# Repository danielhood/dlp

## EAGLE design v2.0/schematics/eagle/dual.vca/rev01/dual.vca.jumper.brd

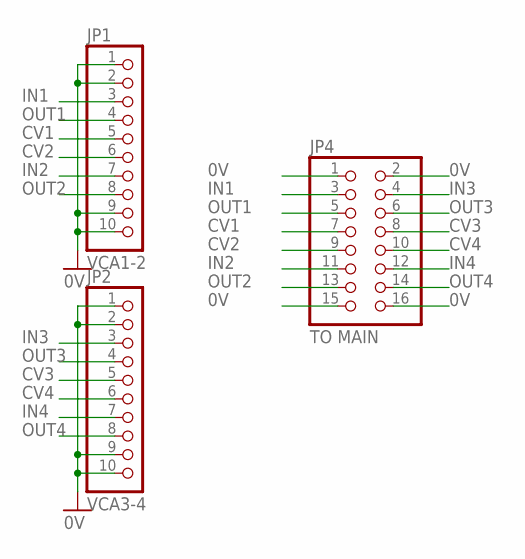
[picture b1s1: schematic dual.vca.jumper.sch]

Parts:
JP1: VCA1-2; 1X10
JP2: VCA3-4; 1X10
JP4: TO MAIN; 2X08

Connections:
0V: JP1.1, JP1.2, JP1.9, JP1.10, JP2.1, JP2.2, JP2.9, JP2.10, JP4.1, JP4.2, JP4.15, JP4.16
CV1: JP1.5, JP4.7
CV2: JP1.6, JP4.9
CV3: JP2.5, JP4.8
CV4: JP2.6, JP4.10
IN1: JP1.3, JP4.3
IN2: JP1.7, JP4.11
IN3: JP2.3, JP4.4
IN4: JP2.7, JP4.12
OUT1: JP1.4, JP4.5
OUT2: JP1.8, JP4.13
OUT3: JP2.4, JP4.6
OUT4: JP2.8, JP4.14

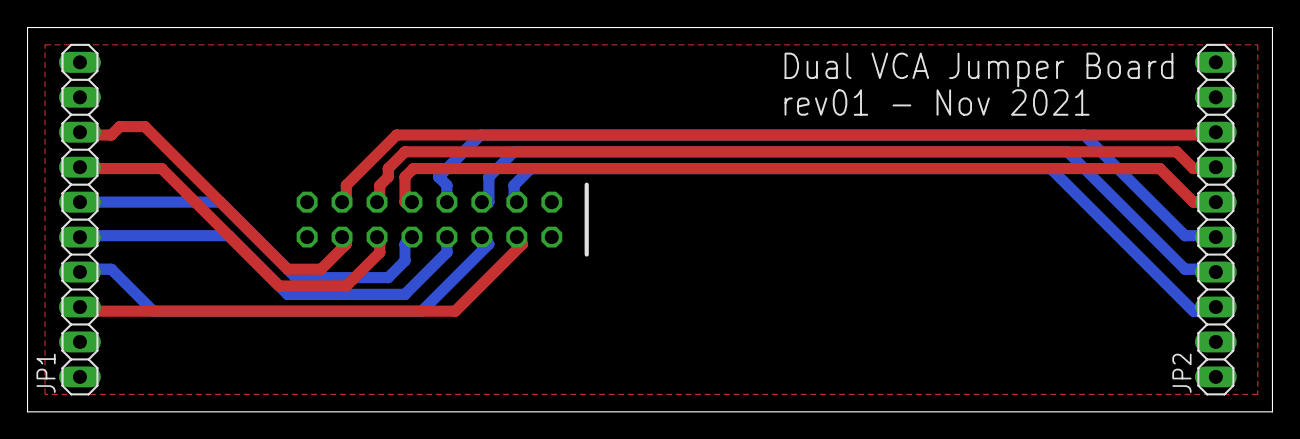
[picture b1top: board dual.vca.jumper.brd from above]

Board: 2 copper layers, 90.5 x 27.9 mm, 3 parts (1 on the bottom side), 13 nets.

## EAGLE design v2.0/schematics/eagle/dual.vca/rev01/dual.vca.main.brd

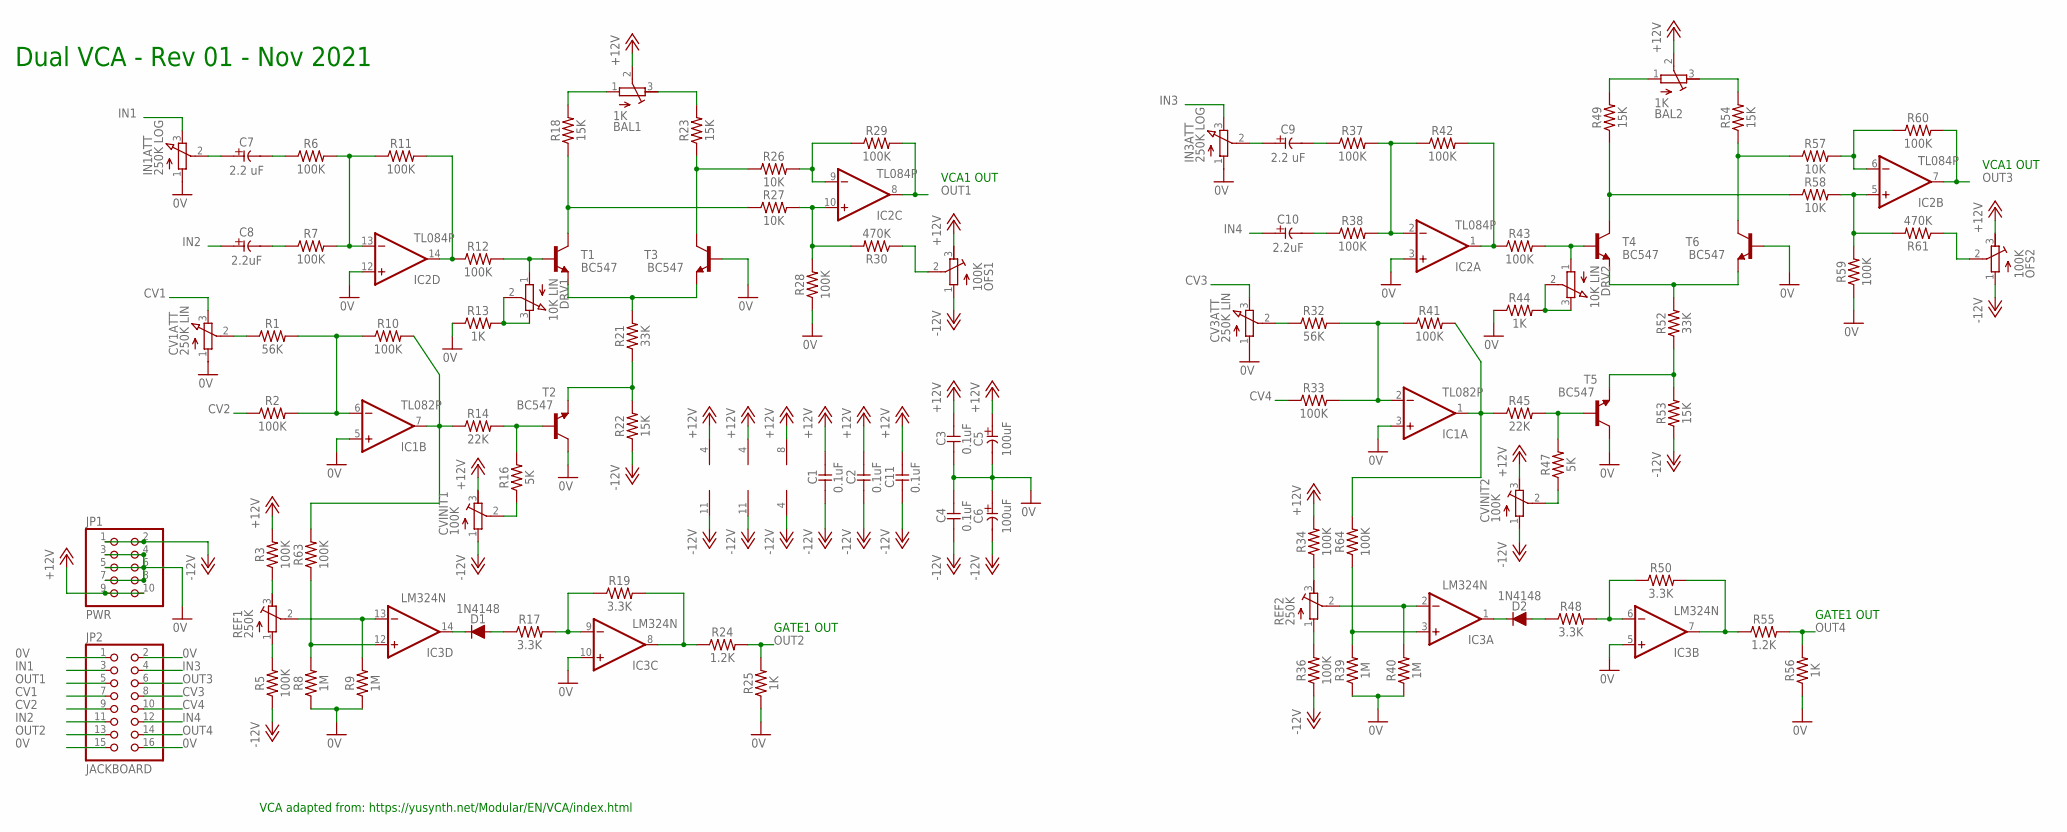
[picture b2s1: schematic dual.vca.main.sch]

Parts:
BAL1, BAL2: 1K; RTRIM3339P
C1, C2, C3, C4, C11: 0.1uF; C025-024X044
C5, C6: 100uF; E5-8,5
C7, C9: 2.2 uF; E2-5
C8, C10: 2.2uF; E2-5
CV1ATT, CV3ATT: 250K LIN; 3RP/1610N
CVINIT1, CVINIT2: 100K; RTRIM3339P
D1, D2: 1N4148; DO34-5
DRV1, DRV2: 10K LIN; 3RP/1610N
IC1: TL082P; DIL08
IC2: TL084P; DIL14
IC3: LM324N; DIL14
IN1ATT, IN3ATT: 250K LOG; 3RP/1610N
JP1: PWR; 2X05
JP2: JACKBOARD; 2X08
OFS1, OFS2: 100K; RTRIM3339P
R1, R32: 56K; 0207/7
R2, R3, R5, R6, R7, R10, R11, R12, R28, R29, R33, R34, R36, R37, R38, R41, R42, R43, R59, R60, R63, R64: 100K; 0207/7
R8, R9, R39, R40: 1M; 0207/7
R13, R25, R44, R56: 1K; 0207/7
R14, R45: 22K; 0207/7
R16, R47: 5K; 0207/7
R17, R19, R48, R50: 3.3K; 0207/7
R18, R22, R23, R49, R53, R54: 15K; 0207/7
R21, R52: 33K; 0207/7
R24, R55: 1.2K; 0207/7
R26, R27, R57, R58: 10K; 0207/7
R30, R61: 470K; 0207/7
REF1, REF2: 250K; RTRIM3339P
T1, T2, T3, T4, T5, T6: BC547; TO92

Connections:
0V: C3.2, C4.1, C5.-, C6.+, CV1ATT.1 (A), CV3ATT.1 (A), IC1.3 (+IN), IC1.5 (+IN), IC2.3 (+IN), IC2.12 (+IN), IC3.5 (+IN), IC3.10 (+IN), IN1ATT.1 (A), IN3ATT.1 (A), JP1.3, JP1.4, JP1.5, JP1.6, JP1.7, JP1.8, JP2.1, JP2.2, JP2.15, JP2.16, R8.1, R9.1, R13.1, R25.1, R28.1, R39.1, R40.1, R44.1, R56.1, R59.1, T2.3 (C), T3.2 (B), T5.3 (C), T6.2 (B)
+12V: BAL1.2 (S), BAL2.2 (S), C1.1, C2.1, C3.1, C5.+, C11.1, CVINIT1.3 (E), CVINIT2.3 (E), IC1.8 (V+), IC2.4 (V+), IC3.4 (V+), JP1.9, JP1.10, OFS1.3 (E), OFS2.3 (E), R3.2, R34.2
-12V: C1.2, C2.2, C4.2, C6.-, C11.2, CVINIT1.1 (A), CVINIT2.1 (A), IC1.4 (V-), IC2.11 (V-), IC3.11 (V-), JP1.1, JP1.2, OFS1.1 (A), OFS2.1 (A), R5.1, R22.1, R36.1, R53.1
CV1: CV1ATT.3 (E), JP2.7
CV2: JP2.9, R2.1
CV3: CV3ATT.3 (E), JP2.8
CV4: JP2.10, R33.1
IN1: IN1ATT.3 (E), JP2.3
IN2: C8.+, JP2.11
IN3: IN3ATT.3 (E), JP2.4
IN4: C10.+, JP2.12
unnamed: IC2.13 (-IN), R6.2, R7.2, R11.1
unnamed: IC2.9 (-IN), R26.2, R29.1
unnamed: IC2.14 (OUT), R11.2, R12.1
unnamed: DRV1.1 (A), R12.2, T1.2 (B)
unnamed: R18.1, R27.1, T1.3 (C)
unnamed: BAL1.1 (A), R18.2
unnamed: BAL1.3 (E), R23.2
unnamed: R23.1, R26.1, T3.3 (C)
unnamed: R21.2, T1.1 (E), T3.1 (E)
unnamed: OFS1.2 (S), R30.1
unnamed: C7.-, R6.1
unnamed: IC2.10 (+IN), R27.2, R28.2, R30.2
unnamed: R21.1, R22.2, T2.1 (E)
unnamed: C8.-, R7.1
unnamed: R14.2, R16.2, T2.2 (B)
unnamed: CVINIT1.2 (S), R16.1
unnamed: IC1.7 (OUT), R10.2, R14.1, R63.2
unnamed: IC3.13 (-IN), R9.2, REF1.2 (S)
unnamed: IC1.6 (-IN), R1.2, R2.2, R10.1
unnamed: R3.1, REF1.3 (E)
unnamed: R5.2, REF1.1 (A)
unnamed: D1.C, IC3.14 (OUT)
unnamed: D1.A, R17.1
unnamed: IC3.9 (-IN), R17.2, R19.1
unnamed: IC3.8 (OUT), R19.2, R24.1
unnamed: DRV2.2 (S), DRV2.3 (E), R44.2
unnamed: C7.+, IN1ATT.2 (S)
unnamed: IC2.2 (-IN), R37.2, R38.2, R42.1
unnamed: CV1ATT.2 (S), R1.1
unnamed: IC2.1 (OUT), R42.2, R43.1
unnamed: R49.1, R58.1, T4.3 (C)
unnamed: BAL2.1 (A), R49.2
unnamed: BAL2.3 (E), R54.2
unnamed: R54.1, R57.1, T6.3 (C)
unnamed: R52.2, T4.1 (E), T6.1 (E)
unnamed: IC2.6 (-IN), R57.2, R60.1
unnamed: IC2.5 (+IN), R58.2, R59.2, R61.2
unnamed: OFS2.2 (S), R61.1
unnamed: R52.1, R53.2, T5.1 (E)
unnamed: R45.2, R47.2, T5.2 (B)
unnamed: CVINIT2.2 (S), R47.1
unnamed: IC1.1 (OUT), R41.2, R45.1, R64.2
unnamed: IC1.2 (-IN), R32.2, R33.2, R41.1
unnamed: C9.-, R37.1
unnamed: C10.-, R38.1
unnamed: IC3.3 (+IN), R39.2, R64.1
unnamed: R34.1, REF2.3 (E)
unnamed: R36.2, REF2.1 (A)
unnamed: D2.C, IC3.1 (OUT)
unnamed: D2.A, R48.1
unnamed: IC3.6 (-IN), R48.2, R50.1
unnamed: IC3.7 (OUT), R50.2, R55.1
unnamed: DRV2.1 (A), R43.2, T4.2 (B)
unnamed: DRV1.2 (S), DRV1.3 (E), R13.2
unnamed: C9.+, IN3ATT.2 (S)
unnamed: CV3ATT.2 (S), R32.1
unnamed: IC3.12 (+IN), R8.2, R63.1
unnamed: IC3.2 (-IN), R40.2, REF2.2 (S)
OUT1: IC2.8 (OUT), JP2.5, R29.2
OUT2: JP2.13, R24.2, R25.2
OUT3: IC2.7 (OUT), JP2.6, R60.2
OUT4: JP2.14, R55.2, R56.2

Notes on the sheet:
VCA adapted from: https://yusynth.net/Modular/EN/VCA/index.html
GATE1 OUT
VCA1 OUT
Dual VCA - Rev 01 - Nov 2021

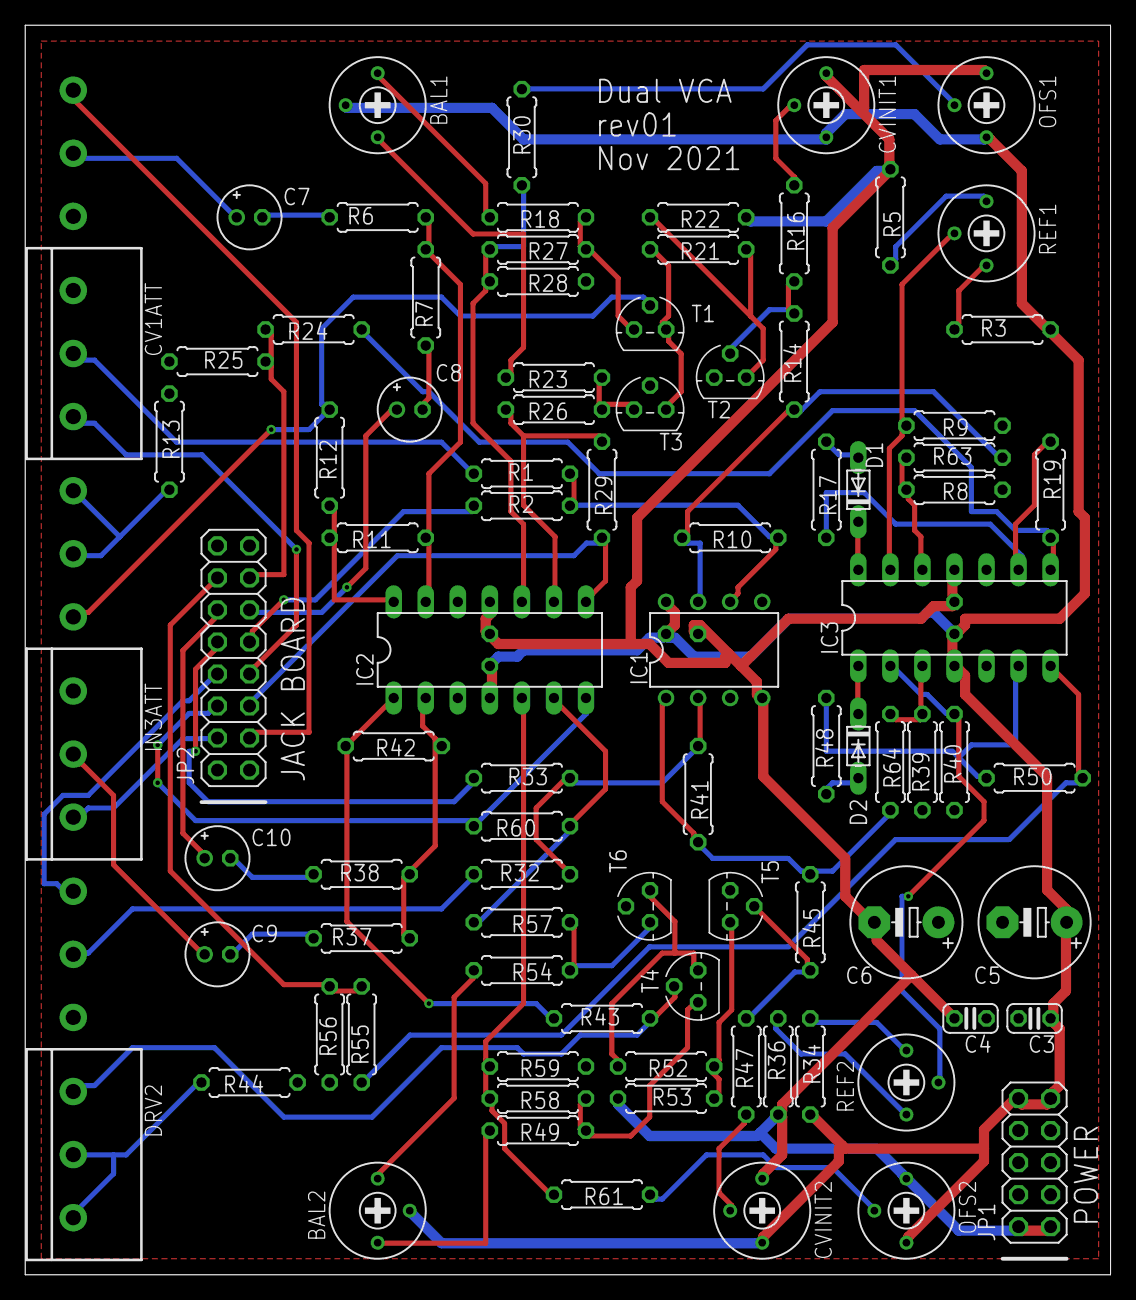
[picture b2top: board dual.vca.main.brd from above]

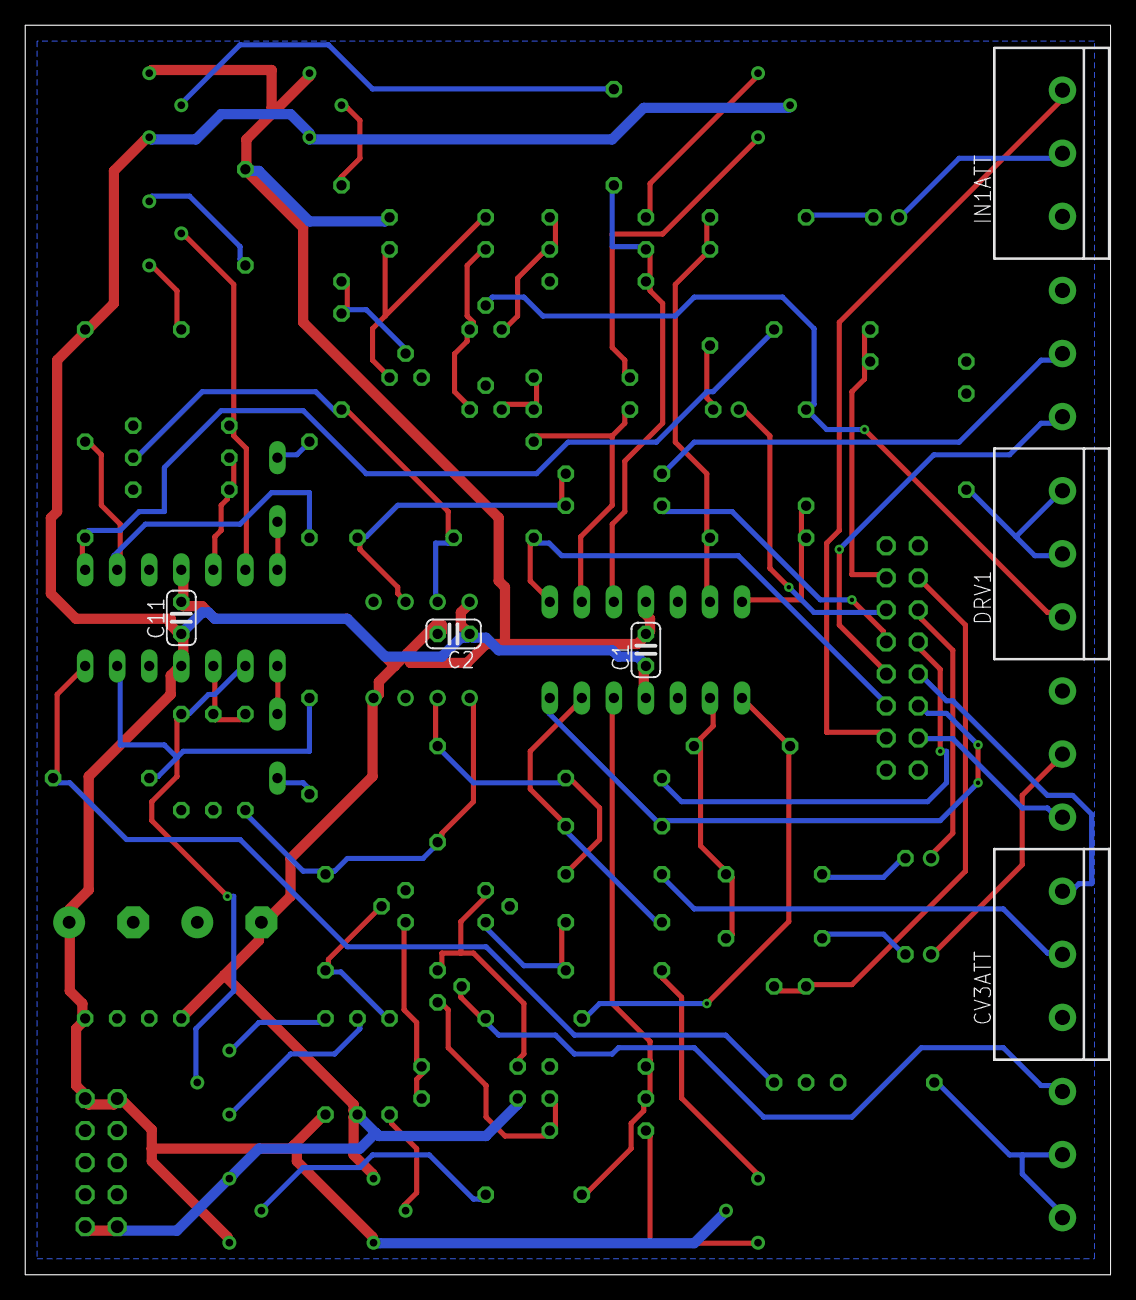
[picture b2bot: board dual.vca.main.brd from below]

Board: 2 copper layers, 86.0 x 99.0 mm, 94 parts (6 on the bottom side), 73 nets.

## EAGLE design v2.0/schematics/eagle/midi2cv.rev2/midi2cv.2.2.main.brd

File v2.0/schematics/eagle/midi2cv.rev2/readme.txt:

midi2cv - rev2
==============
- Opened rev2 on 2016-02-08
- Reomved 0V from all switched outputs

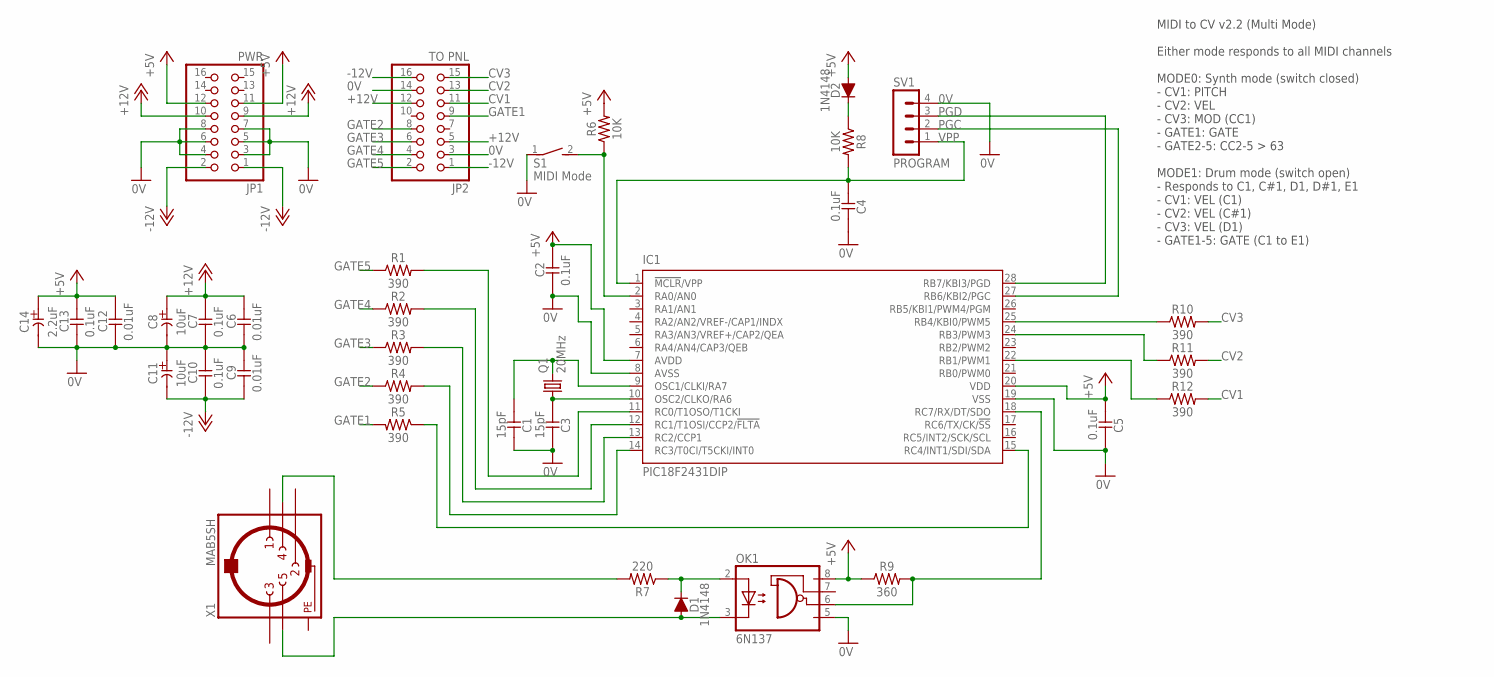
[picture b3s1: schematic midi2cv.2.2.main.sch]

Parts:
C1, C3: 15pF; C025-024X044
C2, C4, C5, C7, C10, C13: 0.1uF; C025-024X044
C6, C9, C12: 0.01uF; C025-024X044
C8, C11: 10uF; E2-5
C14: 2.2uF; E2-5
D1, D2: 1N4148; DO35-7
IC1: PIC18F2431DIP; DIL28-3
JP1: PWR; 2X08
JP2: TO PNL; 2X08
OK1: 6N137; DIL08
Q1: 20MHz; HC49/S
R1, R2, R3, R4, R5, R10, R11, R12: 390; 0309/10
R6, R8: 10K; 0309/10
R7: 220; 0309/10
R9: 360; 0309/10
S1: MIDI Mode; DS-01
SV1: PROGRAM; MA04-1
X1: MAB5SH

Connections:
0V: C1.1, C2.2, C3.1, C4.1, C5.1, C6.2, C7.2, C8.-, C9.1, C10.1, C11.+, C12.2, C13.2, C14.-, IC1.8 (AVSS), IC1.19 (VSS), JP1.3, JP1.4, JP1.5, JP1.6, JP1.7, JP1.8, JP2.3, JP2.14, OK1.5 (GND), S1.1, SV1.4
+5V: C2.1, C5.2, C12.1, C13.1, C14.+, D2.A, IC1.7 (AVDD), IC1.20 (VDD), JP1.11, JP1.12, OK1.8 (VCC), R6.2, R9.1
+12V: C6.1, C7.1, C8.+, JP1.9, JP1.10, JP2.5, JP2.12
-12V: C9.2, C10.2, C11.-, JP1.1, JP1.2, JP2.1, JP2.16
CV1: JP2.11, R12.2
CV2: JP2.13, R11.2
CV3: JP2.15, R10.2
GATE1: JP2.9, R5.2
GATE2: JP2.8, R4.1
GATE3: JP2.6, R3.1
GATE4: JP2.4, R2.1
GATE5: JP2.2, R1.1
unnamed: D2.C, R8.1
unnamed: C3.2, IC1.10 (OSC2/CLKO/RA6), Q1.1
unnamed: R7.2, X1.4
unnamed: D1.A, OK1.3 (C), X1.5
unnamed: D1.C, OK1.2 (A), R7.1
unnamed: IC1.18 (RC7/RX/DT/SDO), OK1.6 (VO), R9.2
unnamed: IC1.25 (RB4/KBI0/PWM5), R10.1
unnamed: IC1.24 (RB3/PWM3), R11.1
unnamed: IC1.22 (RB1/PWM1), R12.1
unnamed: IC1.15 (RC4/INT1/SDI/SDA), R5.1
unnamed: IC1.2 (RA0/AN0), R6.1, S1.2
unnamed: IC1.11 (RC0/T1OSO/T1CKI), R1.2
unnamed: C1.2, IC1.9 (OSC1/CLKI/RA7), Q1.2
unnamed: IC1.12 (RC1/T1OSI/CCP2/!FLTA), R2.2
unnamed: IC1.13 (RC2/CCP1), R3.2
unnamed: IC1.14 (RC3/T0CI/T5CKI/INT0), R4.2
PE: X1.PE, X1.PE@ (PE)
PGC: IC1.27 (RB6/KBI2/PGC), SV1.2
PGD: IC1.28 (RB7/KBI3/PGD), SV1.3
VPP: C4.2, IC1.1 (!MCLR!/VPP), R8.2, SV1.1

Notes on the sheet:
MIDI to CV v2.2 (Multi Mode) Either mode responds to all MIDI channels MODE0: Synth mode (switch closed) - CV1: PITCH - CV2: VEL - CV3: MOD (CC1) - GATE1: GATE - GATE2-5: CC2-5 > 63 MODE1: Drum mode (switch open) - Responds to C1, C#1, D1, D#1, E1 - CV1: VEL (C1) - CV2: VEL (C#1) - CV3: VEL (D1) - 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

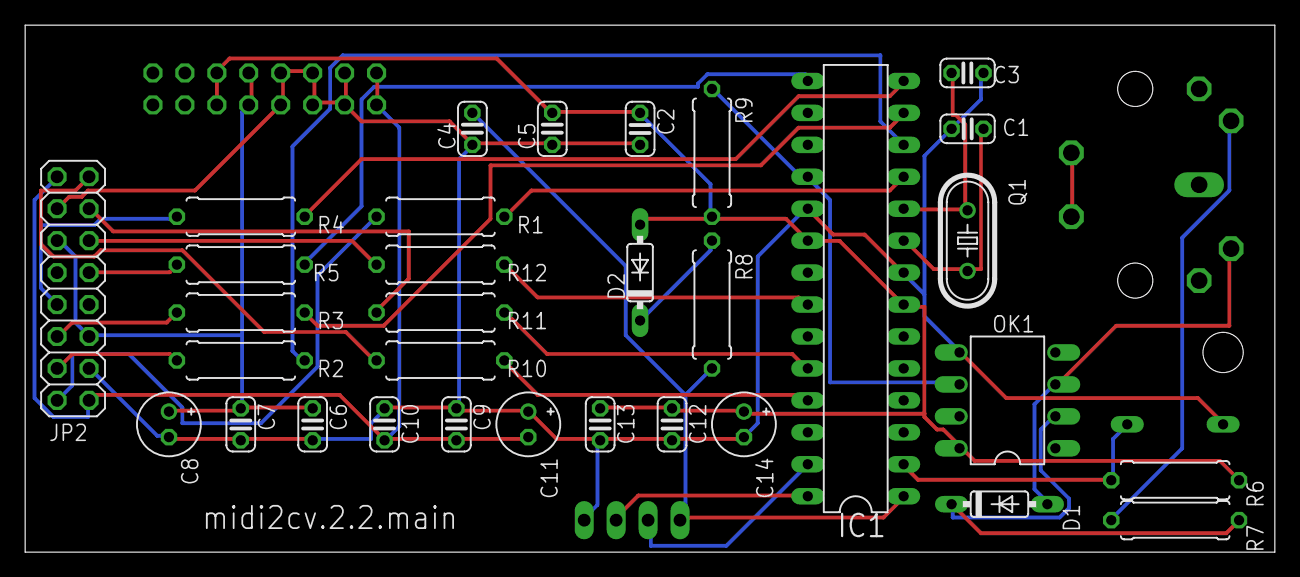
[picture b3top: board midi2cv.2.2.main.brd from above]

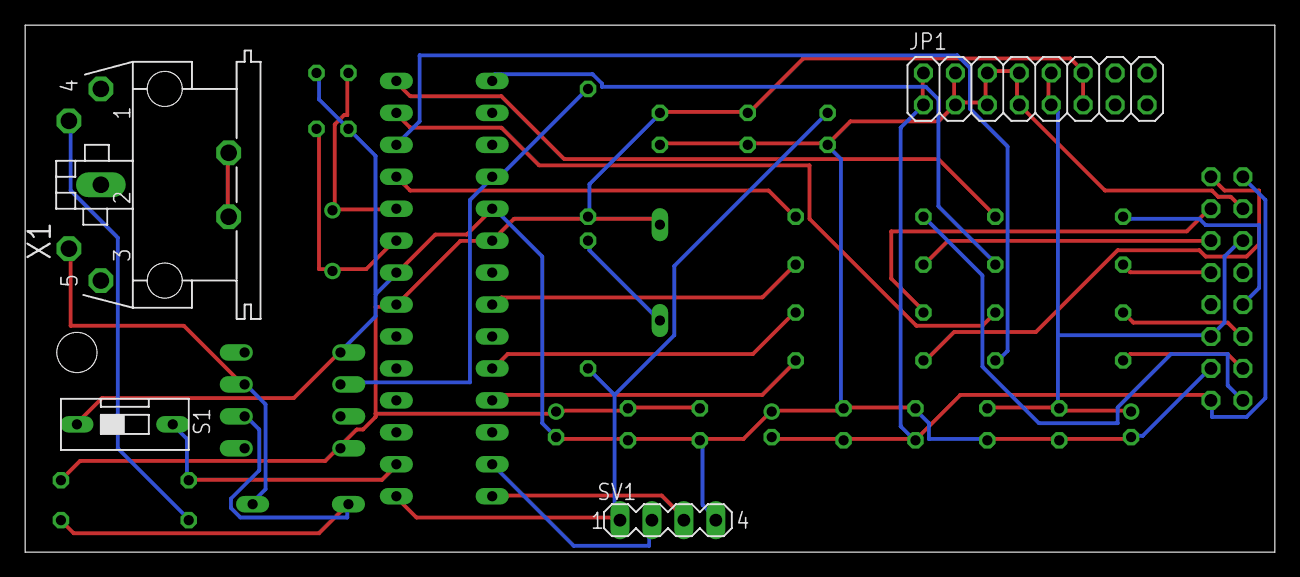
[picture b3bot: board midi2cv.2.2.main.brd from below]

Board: 2 copper layers, 99.4 x 41.9 mm, 36 parts (4 on the bottom side), 32 nets.

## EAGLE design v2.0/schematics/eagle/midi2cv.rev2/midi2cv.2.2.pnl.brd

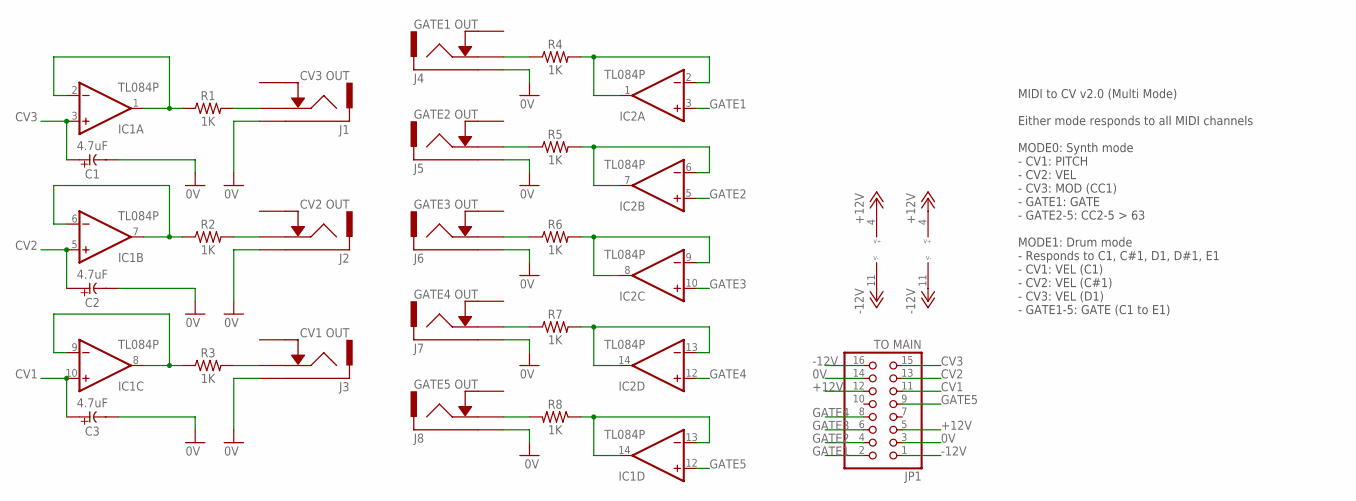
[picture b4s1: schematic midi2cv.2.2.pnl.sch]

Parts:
C1, C2, C3: 4.7uF; E2-5
IC1, IC2: TL084P; DIL14
J1: CV3 OUT; ACJM-MV35-2S
J2: CV2 OUT; ACJM-MV35-2S
J3: CV1 OUT; ACJM-MV35-2S
J4: GATE1 OUT; ACJM-MV35-2S
J5: GATE2 OUT; ACJM-MV35-2S
J6: GATE3 OUT; ACJM-MV35-2S
J7: GATE4 OUT; ACJM-MV35-2S
J8: GATE5 OUT; ACJM-MV35-2S
JP1: TO MAIN; 2X08
R1, R2, R3, R4, R5, R6, R7, R8: 1K; 0309/10

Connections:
0V: C1.-, C2.-, C3.-, J1.P$1, J2.P$1, J3.P$1, J4.P$1, J5.P$1, J6.P$1, J7.P$1, J8.P$1, JP1.3, JP1.14
+12V: IC1.4 (V+), IC2.4 (V+), JP1.5, JP1.12
-12V: IC1.11 (V-), IC2.11 (V-), JP1.1, JP1.16
CV1: C3.+, IC1.10 (+IN), JP1.11
CV2: C2.+, IC1.5 (+IN), JP1.13
CV3: C1.+, IC1.3 (+IN), JP1.15
GATE1: IC1.12 (+IN), JP1.9
GATE2: IC2.12 (+IN), JP1.8
GATE3: IC2.10 (+IN), JP1.6
GATE4: IC2.5 (+IN), JP1.4
GATE5: IC2.3 (+IN), JP1.2
unnamed: IC1.1 (OUT), IC1.2 (-IN), R1.1
unnamed: IC1.6 (-IN), IC1.7 (OUT), R2.1
unnamed: IC1.8 (OUT), IC1.9 (-IN), R3.1
unnamed: IC1.13 (-IN), IC1.14 (OUT), R8.1
unnamed: J4.P$3, R4.1
unnamed: J5.P$3, R5.1
unnamed: J6.P$3, R6.1
unnamed: J7.P$3, R7.1
unnamed: J8.P$3, R8.2
unnamed: IC2.13 (-IN), IC2.14 (OUT), R7.2
unnamed: IC2.8 (OUT), IC2.9 (-IN), R6.2
unnamed: IC2.6 (-IN), IC2.7 (OUT), R5.2
unnamed: IC2.1 (OUT), IC2.2 (-IN), R4.2
unnamed: J1.P$3, R1.2
unnamed: J2.P$3, R2.2
unnamed: J3.P$3, R3.2

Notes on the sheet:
MIDI to CV v2.0 (Multi Mode) Either mode responds to all MIDI channels MODE0: Synth mode - CV1: PITCH - CV2: VEL - CV3: MOD (CC1) - GATE1: GATE - GATE2-5: CC2-5 > 63 MODE1: Drum mode - Responds to C1, C#1, D1, D#1, E1 - CV1: VEL (C1) - CV2: VEL (C#1) - CV3: VEL (D1) - GATE1-5: GATE (C1 to E1)

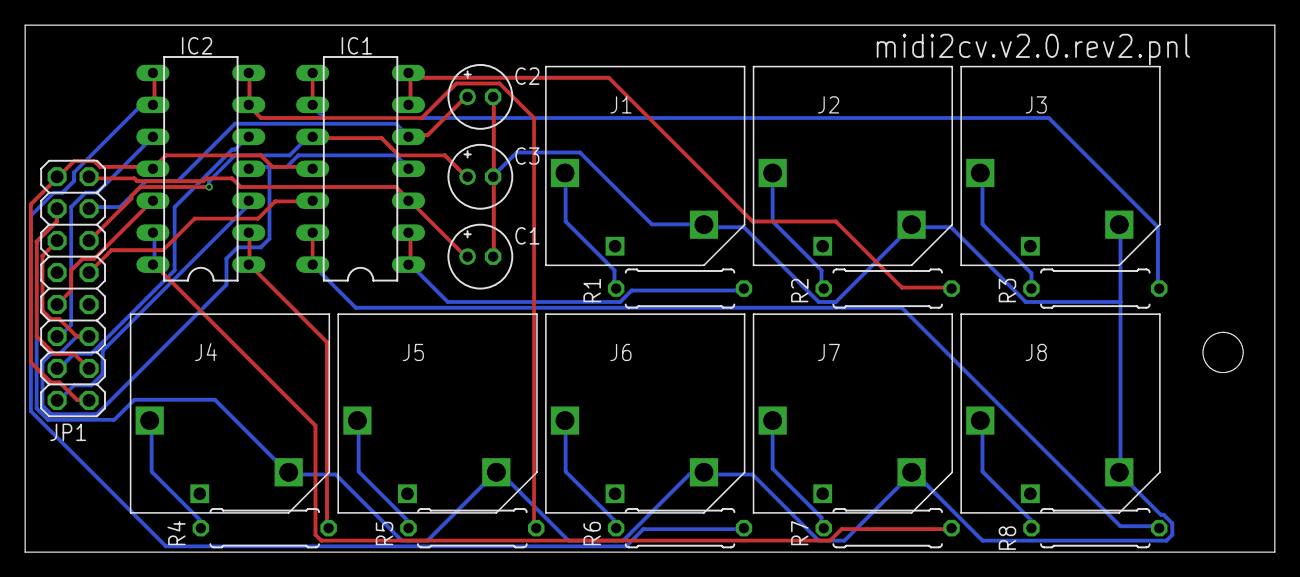
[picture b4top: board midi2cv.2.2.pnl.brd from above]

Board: 2 copper layers, 99.4 x 41.9 mm, 22 parts (0 on the bottom side), 27 nets.

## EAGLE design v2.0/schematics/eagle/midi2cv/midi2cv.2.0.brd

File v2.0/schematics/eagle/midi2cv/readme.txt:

midi2cv - rev1
==============
- Sent both PNL and MAIN to SEEED Studio 2016-02-07

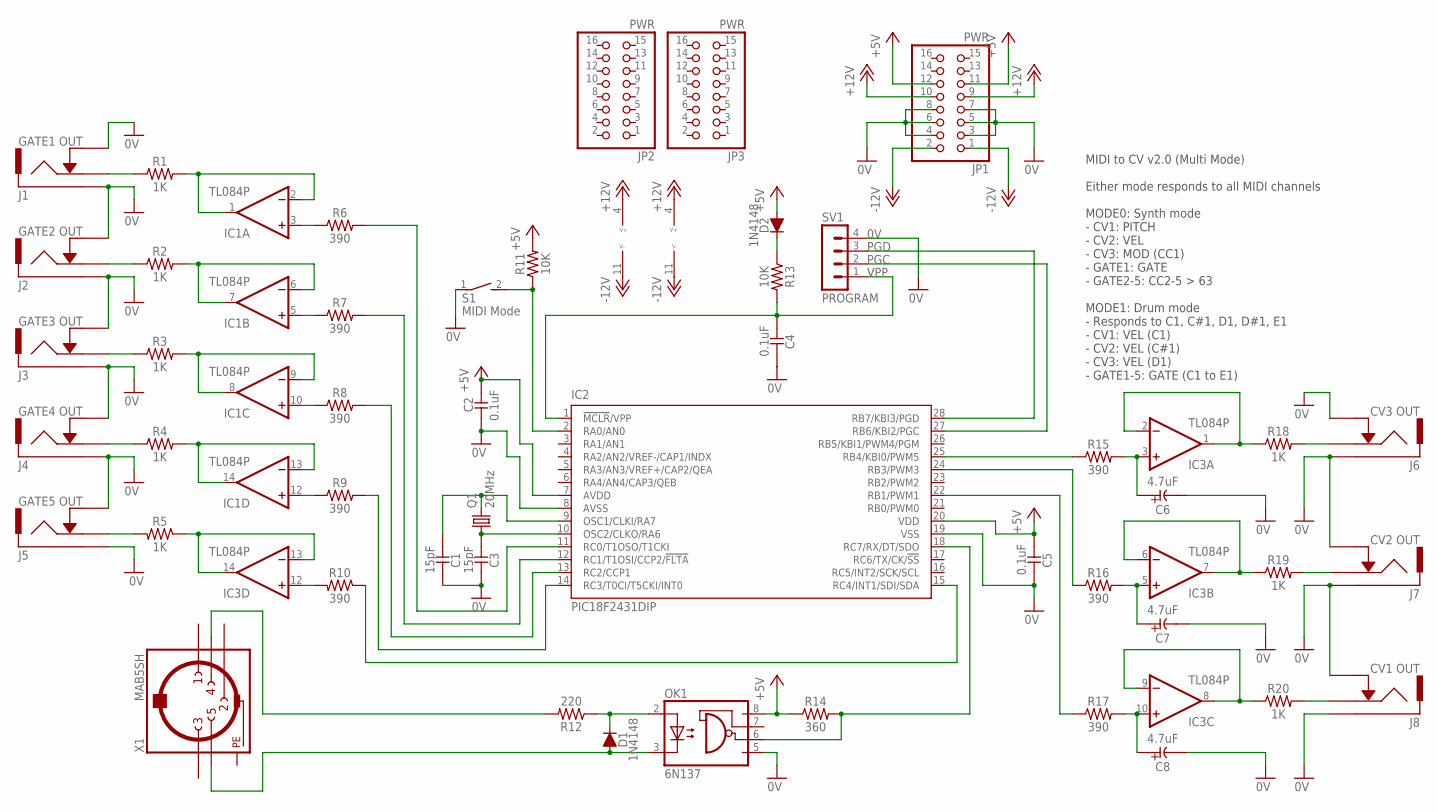
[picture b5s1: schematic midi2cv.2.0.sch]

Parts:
C1, C3: 15pF; C025-024X044
C2, C4, C5: 0.1uF; C025-024X044
C6, C7, C8: 4.7uF; E2-5
D1, D2: 1N4148; DO35-7
IC1, IC3: TL084P; DIL14
IC2: PIC18F2431DIP; DIL28-3
J1: GATE1 OUT; ACJM-MV35-2S
J2: GATE2 OUT; ACJM-MV35-2S
J3: GATE3 OUT; ACJM-MV35-2S
J4: GATE4 OUT; ACJM-MV35-2S
J5: GATE5 OUT; ACJM-MV35-2S
J6: CV3 OUT; ACJM-MV35-2S
J7: CV2 OUT; ACJM-MV35-2S
J8: CV1 OUT; ACJM-MV35-2S
JP1, JP2, JP3: PWR; 2X08
OK1: 6N137; DIL08
Q1: 20MHz; HC49/S
R1, R2, R3, R4, R5, R18, R19, R20: 1K; 0309/10
R6, R7, R8, R9, R10, R15, R16, R17: 390; 0309/10
R11, R13: 10K; 0309/10
R12: 220; 0309/10
R14: 360; 0309/10
S1: MIDI Mode; DS-01
SV1: PROGRAM; MA04-1
X1: MAB5SH

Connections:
0V: C1.1, C2.2, C3.1, C4.1, C5.1, C6.-, C7.-, C8.-, IC2.8 (AVSS), IC2.19 (VSS), J1.P$1, J1.P$3, J2.P$1, J2.P$3, J3.P$1, J3.P$3, J4.P$1, J4.P$3, J5.P$1, J5.P$3, J6.P$1, J6.P$3, J7.P$1, J7.P$3, J8.P$1, J8.P$3, JP1.3, JP1.4, JP1.5, JP1.6, JP1.7, JP1.8, OK1.5 (GND), S1.1, SV1.4
+5V: C2.1, C5.2, D2.A, IC2.7 (AVDD), IC2.20 (VDD), JP1.11, JP1.12, OK1.8 (VCC), R11.2, R14.1
+12V: IC1.4 (V+), IC3.4 (V+), JP1.9, JP1.10
-12V: IC1.11 (V-), IC3.11 (V-), JP1.1, JP1.2
unnamed: D2.C, R13.1
unnamed: IC3.1 (OUT), IC3.2 (-IN), R18.1
unnamed: IC3.6 (-IN), IC3.7 (OUT), R19.1
unnamed: IC3.8 (OUT), IC3.9 (-IN), R20.1
unnamed: IC1.5 (+IN), R7.1
unnamed: C3.2, IC2.10 (OSC2/CLKO/RA6), Q1.1
unnamed: IC3.13 (-IN), IC3.14 (OUT), R5.1
unnamed: C6.+, IC3.3 (+IN), R15.2
unnamed: R12.2, X1.4
unnamed: D1.A, OK1.3 (C), X1.5
unnamed: D1.C, OK1.2 (A), R12.1
unnamed: C7.+, IC3.5 (+IN), R16.2
unnamed: IC2.18 (RC7/RX/DT/SDO), OK1.6 (VO), R14.2
unnamed: C8.+, IC3.10 (+IN), R17.2
unnamed: IC3.12 (+IN), R10.2
unnamed: IC2.25 (RB4/KBI0/PWM5), R15.1
unnamed: IC2.24 (RB3/PWM3), R16.1
unnamed: IC2.22 (RB1/PWM1), R17.1
unnamed: IC2.15 (RC4/INT1/SDI/SDA), R10.1
unnamed: IC2.2 (RA0/AN0), R11.1, S1.2
unnamed: J1.P$2, R1.1
unnamed: J2.P$2, R2.1
unnamed: J3.P$2, R3.1
unnamed: J4.P$2, R4.1
unnamed: J5.P$2, R5.2
unnamed: IC2.11 (RC0/T1OSO/T1CKI), R6.2
unnamed: C1.2, IC2.9 (OSC1/CLKI/RA7), Q1.2
unnamed: IC2.12 (RC1/T1OSI/CCP2/!FLTA), R7.2
unnamed: IC2.13 (RC2/CCP1), R8.2
unnamed: IC2.14 (RC3/T0CI/T5CKI/INT0), R9.2
unnamed: IC1.13 (-IN), IC1.14 (OUT), R4.2
unnamed: IC1.12 (+IN), R9.1
unnamed: IC1.10 (+IN), R8.1
unnamed: IC1.3 (+IN), R6.1
unnamed: IC1.8 (OUT), IC1.9 (-IN), R3.2
unnamed: IC1.6 (-IN), IC1.7 (OUT), R2.2
unnamed: IC1.1 (OUT), IC1.2 (-IN), R1.2
unnamed: J6.P$2, R18.2
unnamed: J7.P$2, R19.2
unnamed: J8.P$2, R20.2
PE: X1.PE, X1.PE@ (PE)
PGC: IC2.27 (RB6/KBI2/PGC), SV1.2
PGD: IC2.28 (RB7/KBI3/PGD), SV1.3
VPP: C4.2, IC2.1 (!MCLR!/VPP), R13.2, SV1.1

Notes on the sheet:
MIDI to CV v2.0 (Multi Mode) Either mode responds to all MIDI channels MODE0: Synth mode - CV1: PITCH - CV2: VEL - CV3: MOD (CC1) - GATE1: GATE - GATE2-5: CC2-5 > 63 MODE1: Drum mode - Responds to C1, C#1, D1, D#1, E1 - CV1: VEL (C1) - CV2: VEL (C#1) - CV3: VEL (D1) - GATE1-5: GATE (C1 to E1)

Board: 2 copper layers, 49 parts (1 on the bottom side), 48 nets, no tracks yet.
